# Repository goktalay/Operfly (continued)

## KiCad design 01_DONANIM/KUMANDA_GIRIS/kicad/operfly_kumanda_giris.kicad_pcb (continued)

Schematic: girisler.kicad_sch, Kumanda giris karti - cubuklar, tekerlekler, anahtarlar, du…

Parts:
C13, C14, C15, C16, C17, C18, C19, C20, C21, C22, C23, C24, C25, C26, C27, C28: 100n; C_0402_1005Metric
J3: Cubuk sol; JST_GH_SM04B-GHS-TB_1x04-1MP_P1.25mm_Horizontal
J4: Cubuk sag; JST_GH_SM04B-GHS-TB_1x04-1MP_P1.25mm_Horizontal
J5: Tekerlek sol; JST_GH_SM03B-GHS-TB_1x03-1MP_P1.25mm_Horizontal
J6: Tekerlek sag; JST_GH_SM03B-GHS-TB_1x03-1MP_P1.25mm_Horizontal
J7: Anahtar A; JST_GH_SM03B-GHS-TB_1x03-1MP_P1.25mm_Horizontal
J8: Anahtar B; JST_GH_SM03B-GHS-TB_1x03-1MP_P1.25mm_Horizontal
J9: Anahtar C; JST_GH_SM03B-GHS-TB_1x03-1MP_P1.25mm_Horizontal
J10: Anahtar D; JST_GH_SM03B-GHS-TB_1x03-1MP_P1.25mm_Horizontal
J11: Anahtar E; JST_GH_SM03B-GHS-TB_1x03-1MP_P1.25mm_Horizontal
J12: Anahtar F; JST_GH_SM03B-GHS-TB_1x03-1MP_P1.25mm_Horizontal
J13: Yon tusu; JST_GH_SM06B-GHS-TB_1x06-1MP_P1.25mm_Horizontal
J14: Dugme 1; JST_GH_SM02B-GHS-TB_1x02-1MP_P1.25mm_Horizontal
J15: Dugme 2; JST_GH_SM02B-GHS-TB_1x02-1MP_P1.25mm_Horizontal
R15, R16, R17, R18, R19, R21, R25, R28, R31, R34, R37, R40, R48, R50: 1k; R_0402_1005Metric
R20, R22: 1M; R_0402_1005Metric
R23, R24, R26, R27, R29, R30, R32, R33, R35, R36, R38, R39: 47k; R_0402_1005Metric
R41, R45, R47, R49: 10k; R_0402_1005Metric
R42: 0R; R_0402_1005Metric
R43: 2k2; R_0402_1005Metric
R44: 4k7; R_0402_1005Metric
R46: 22k; R_0402_1005Metric

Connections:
+3V3: R47.1, R49.1; also elsewhere on the board
+3V3A: C17.1, J3.1, J4.1, J5.1, J6.1, J7.1, J8.1, J9.1, J10.1, J11.1, J12.1, R23.1, R26.1, R29.1, R32.1, R35.1, R38.1, R41.1; also elsewhere on the board
BTN_1: C27.1, R47.2, R48.2; also elsewhere on the board
BTN_1_J: J14.1, R48.1
BTN_2: C28.1, R49.2, R50.2; also elsewhere on the board
BTN_2_J: J15.1, R50.1
GIM_L_X: C13.1, R15.2; also elsewhere on the board
GIM_L_X_J: J3.2, R15.1
GIM_L_Y: C14.1, R16.2; also elsewhere on the board
GIM_L_Y_J: J3.3, R16.1
GIM_R_X: C15.1, R17.2; also elsewhere on the board
GIM_R_X_J: J4.2, R17.1
GIM_R_Y: C16.1, R18.2; also elsewhere on the board
GIM_R_Y_J: J4.3, R18.1
GND: C13.2, C14.2, C15.2, C16.2, C17.2, C18.2, C19.2, C20.2, C21.2, C22.2, C23.2, C24.2, C25.2, C26.2, C27.2, C28.2, J3.4, J3.MP (MountPin), J4.4, J4.MP (MountPin), J5.3, J5.MP (MountPin), J6.3, J6.MP (MountPin), J7.3, J7.MP (MountPin), J8.3, J8.MP (MountPin), J9.3, J9.MP (MountPin), J10.3, J10.MP (MountPin), J11.3, J11.MP (MountPin), J12.3, J12.MP (MountPin), J13.1, J13.MP (MountPin), J14.2, J14.MP (MountPin), J15.2, J15.MP (MountPin), R20.2, R22.2, R24.2, R27.2, R30.2, R33.2, R36.2, R39.2; also elsewhere on the board
NAV_ADC: C26.1, R41.2, R42.2, R43.2, R44.2, R45.2, R46.2; also elsewhere on the board
NAV_C: J13.2, R42.1
NAV_D: J13.4, R44.1
NAV_L: J13.5, R45.1
NAV_R: J13.6, R46.1
NAV_U: J13.3, R43.1
SW_A: C20.1, R25.2; also elsewhere on the board
SW_A_J: J7.2, R23.2, R24.1, R25.1
SW_B: C21.1, R28.2; also elsewhere on the board
SW_B_J: J8.2, R26.2, R27.1, R28.1
SW_C: C22.1, R31.2; also elsewhere on the board
SW_C_J: J9.2, R29.2, R30.1, R31.1
SW_D: C23.1, R34.2; also elsewhere on the board
SW_D_J: J10.2, R32.2, R33.1, R34.1
SW_E: C24.1, R37.2; also elsewhere on the board
SW_E_J: J11.2, R35.2, R36.1, R37.1
SW_F: C25.1, R40.2; also elsewhere on the board
SW_F_J: J12.2, R38.2, R39.1, R40.1
WHEEL_L: C18.1, R19.2, R20.1; also elsewhere on the board
WHEEL_L_J: J5.2, R19.1
WHEEL_R: C19.1, R21.2, R22.1; also elsewhere on the board
WHEEL_R_J: J6.2, R21.1

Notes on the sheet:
DUGMELER (anlik basmali, 2 adet): 2 kontak = sinyal, GND. 10 k yukari cekme, 100 nF.
Secilen gimbalin kendi kablosu bu siraya gore uyarlanir. Her giriste 1 k + 100 nF: suzme ve asiri gerilimde akim sinirlama.
TEKERLEKLER (potansiyometre ya da Hall, analog): 3 kontak = +3V3A, sinyal, GND.
bos 3,3 V; orta 0 V; yukari 0,60 V; asagi 1,06 V; sol 1,65 V; sag 2,27 V (10 k yukari cekme ile).
YON TUSU (5 yonlu, menu icin): 6 kontak = GND, orta, yukari, asagi, sol, sag. Her yon farkli direncle tek analog girise baglanir:
CUBUKLAR (Hall etkili gimbal, 3,3 V, eksen basina analog cikis): 4 kontak = +3V3A, X, Y, GND (bizim tanimimiz).
orta konumda iki 47 k giris gerilimini yariya ceker. Tek analog giris uc konumu okur; kopuk kablo da 'orta' gorunur (ariza anlasilir).
ANAHTARLAR A-F (2 ya da 3 konumlu): 3 kontak = +3V3A, ortak uc, GND. Anahtar ortak ucu +3V3A'ya ya da GND'ye baglar;

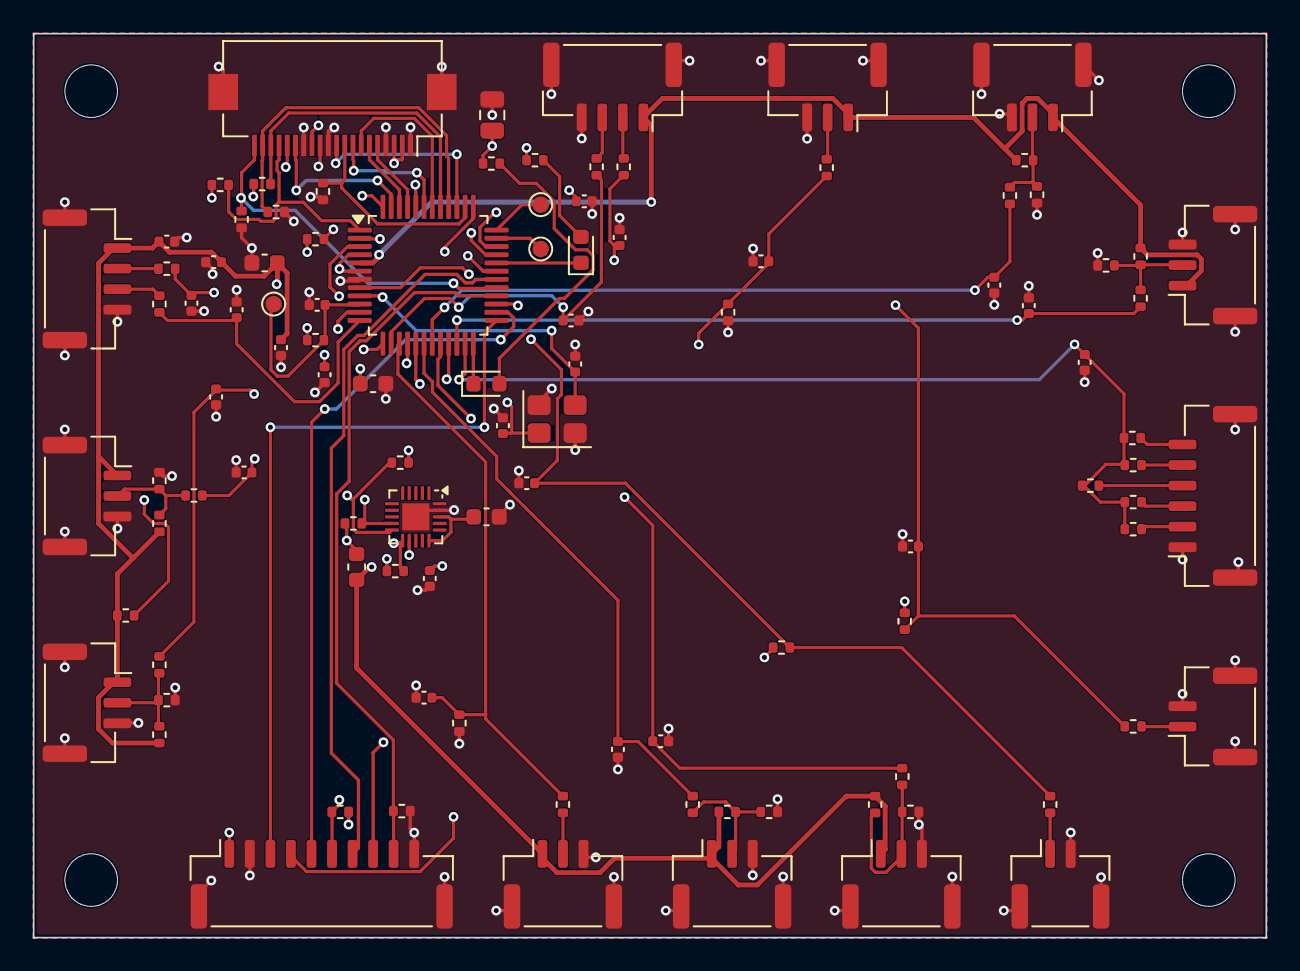
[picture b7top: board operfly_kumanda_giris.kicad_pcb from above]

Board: 4 copper layers, 75.0 x 55.0 mm, 106 parts (0 on the bottom side), 69 nets.

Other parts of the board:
H1, H2, H3, H4: M3; MountingHole_3.2mm_M3

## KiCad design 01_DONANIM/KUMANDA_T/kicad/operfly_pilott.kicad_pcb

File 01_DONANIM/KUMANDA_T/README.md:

# Operfly Pilot T ana kartı (OPFKTL)

12 kanal kumanda eden ve telemetriyi küçük ekranda gösteren model. Bu kart Pilot 12 ana kartının devresini
(batarya, şarj, beslemeler, kumanda radyosu) ve telemetri ekranını taşır; işlemci ve güvenli eleman ortak giriş
kartındadır (`01_DONANIM/KUMANDA_GIRIS`). İki kart arasındaki bağlantı: `13_DOKUMANTASYON/KUMANDA_ARAYUZU.md`.

## Durum (15 Kasım 2026)

- KiCad projesi: `kicad/operfly_pilott.kicad_pro`.
  Üretim ve denetim: `python 10_ORTAK_ARACLAR/kicad/denetle.py KUMANDA_T operfly_pilott`.
- Şematik tamam, 4 sayfa: kök, batarya/şarj/USB/güç/3,3 V (`guc`), radyo ve giriş kartı bağlantısı (`radyo`),
  ekran (`ekran`). ERC 0 hata, 0 uyarı. Kart çizimi başlamadı.
- `guc` ve `radyo` sayfaları Pilot 12 ile ortak kaynaktan üretilir (`10_ORTAK_ARACLAR/kicad/kumanda_ana.py`);
  o sayfaların kararları ve doğrulama listesi `01_DONANIM/KUMANDA_12/README.md` dosyasındadır ve burada da geçerlidir.

## Kararlar (sahibi kararı tasarımcıya bıraktı)

1. **Pilot T = Pilot 12 + ekran.** Güç ve radyo bölümü birebir aynıdır; tek kaynak dosyadan üretilir, bir karttaki
   düzeltme diğerine kendiliğinden geçer. Telemetri kumanda radyosunun aynı bağlantısından gelir; ek radyo yoktur.
2. **Ekran: EA DOGM128W-6** (128 × 64 nokta, görünen alan 51 × 31 mm, siyah-beyaz, yarı geçirgen LCD). Gerekçe:
   güneş altında arka ışıksız okunur (renkli küçük ekranlar güneşte okunmaz), 0,3 mA çeker (batarya süresini
   etkilemez), tek 3,3 V besleme ve SPI ile çalışır, karta doğrudan lehimlenir, tek adet satın alınabilir.
   Telemetri için yeterlidir: 8 satır × 21 karakter ya da büyük rakamlarla 4 satır.
3. **Arka ışık: kehribar (EA LED55X46-A).** 3,3 V'tan yalnızca dirençle çalışır (beyaz arka ışık yükselten sürücü
   isterdi), ömrü 100.000 saattir ve gece gözü kamaştırmaz. İşlemci PWM ile kısar; gündüz kapalı kalabilir.
   Toplam yaklaşık 45 mA.
4. **Ekranı giriş kartındaki işlemci sürer.** Giriş kartının "ekran / genişleme" konnektöründen bu karta 10 telli
   düz kablo gelir (JST-GH 10, iki uçta aynı sıra). Böylece giriş kartı üç kumandada da değişmeden kalır.
5. **Ekran bu kartın 3,3 V'undan beslenir;** kablodaki 3,3 V ucu kullanılmaz (iki besleme yolu birleştirilmez).
6. **Güvenli durum:** kablo takılı değilken ya da işlemci sıfırlanırken ekran sıfırlamada tutulur, arka ışık kapalıdır.
7. **Ekranın iç gerilim yükselticisi kullanılır** (üreticinin tek beslemeli devresi, 9 adet 1 µF kondansatör);
   ayrı bir 12 V kaynağı gerekmez.

## Sahibinin bilmesi gerekenler

- **Ekran küçük ve tek renklidir;** harita ya da video göstermez. Harita ve video Pilot Pro'nun işidir.
- **Ekran ana kartın üstündedir;** kasada ekran penceresi ana kartın yerini belirler. Kasa tasarımında ekranın
  ayrı küçük bir karta alınması gerekirse devre aynen taşınır.
- **Ekran karta elle lehimlenir** (LCD fırın lehimine dayanmaz; üretici 80 °C üstünü yasaklar). Dizgi sonrasında
  ayrı bir işçilik adımıdır.
- **Soğukta ekran yavaşlar:** çalışma aralığı −20…+70 °C. Daha soğukta görüntü geç değişir; kumanda çalışmaya
  devam eder (ekran kumanda yolunun parçası değildir).
- **Çalışma süresi Pilot 12 ile hemen hemen aynıdır;** arka ışık sürekli açıkken yaklaşık 45 mA ek tüketim olur.

## Doğrulanacaklar

- **Ayak izi** (KiCad kütüphanesindeki `Display:EA_DOGM128-6`) üreticinin ölçü çizimiyle ve arka ışıklı yükseklikle
  (5,8 mm) karşılaştırılacak; ekranın bakış yönü (alttan / üstten) kasaya göre seçilecek (yazılım ayarı).
- **Arka ışık akımı ve parlaklığı** numunede ölçülecek; 82 Ω dirençler ve anahtarlama transistörü buna göre
  kesinleşecek. Gece görüş gözlüğüyle kullanım istenirse arka ışık rengi ve en düşük parlaklık ayrıca denenecek.
- **Kontrast ayarı** sıcaklık aralığında numunede denenecek.
- **Askeri sıcaklık aralığı hedefi** (−40 °C) bu ekranla karşılanmaz; gerekirse ısıtıcılı ya da geniş aralıklı
  ekran ayrıca değerlendirilecek.
- **Kablo boyu ve SPI hızı:** 10 telli kablo kısa tutulacak (öneri 10 cm altı); 33 Ω seri dirençlerle denenecek.
- Güç ve radyo bölümünün doğrulama listesi: `01_DONANIM/KUMANDA_12/README.md`.

## Kart çizimi (otomatik)

Sahibinin kararıyla kart **otomatik** çizildi: yerleşim `pcb_yerlesim.py`, yollar dış bir otomatik yol çiziciyle
(`pcb_ciz.py`). Dosya: `kicad/operfly_pilott.kicad_pcb`; ayarlar `kicad/pcb_ayar.py`.
Yeniden üretmek için: `python 10_ORTAK_ARACLAR/kicad/pcb_ciz.py KUMANDA_T operfly_pilott`.

- **Kart:** 135 x 95 mm, 4 katman (üst: elemanlar + sinyal, iç 1: toprak, iç 2: +3V3, alt: sinyal), 100 eleman, tamamı üst yüzde; köşelerde M3 montaj deliği.
- **Kurallar:** yol 0,20 mm, açıklık 0,125 mm, geçiş 0,6/0,3 mm; besleme ağları, ağın en dar ucunu aşmayacak biçimde 0,2-1,0 mm (0,4 mm ve üstünde geçiş 0,8/0,4 mm); bakır-kenar 0,25 mm.
- **Denetim:** DRC 0 ihlal, 0 bağlanmamış uç; şematik-kart uyumu temiz. 857 yol parçası, 151 geçiş.

**Bu bir mühendis çizimi değildir.** Üretimden önce bir kart tasarımcısının bakması gereken noktalar:

- Anten hatları 0,35 mm genişlikte çizildi; 50 ohm empedans üreticinin katman dizilimiyle hesaplanıp doğrulanmadı, hat uzunluğu, kıvrımlar ve geçiş sayısı gözetilmedi. Menzil doğrudan bu hatlara bağlıdır.
- Kenar montajlı SMA konnektörlerinin uçları kart kenarından 0,35 mm içeride başlar; anten hatlarının çevresinde toprak dikiş geçişleri yok.
- Ekranın (EA DOGM128) kart üzerindeki yeri kasadaki ekran penceresine göre seçilmedi; ekranın altında kalan elemanların yüksekliği denetlenmedi.
- Şarj devresi ve regülatörlerin ısıl bakırı ve akım yolları ayrıca hesaplanmadı.
- Kart ölçüsü ve konnektör yerleri kumanda kasasına göre seçilmedi (kasa henüz tasarlanmadı).
- Anahtarlamalı regülatörlerin (bobin, diyot, giriş/çıkış kondansatörleri) akım döngüleri küçük tutulmadı; gürültü ve verim ölçülmeli.
- Kristal ve osilatör hatları en kısa yoldan çizilmedi; altlarından başka sinyal geçip geçmediğine bakılmalı.
- Fark çiftleri (CAN, USB, Ethernet) çift olarak, eşit uzunlukta ve empedans denetimli çizilmedi.
- Güç elemanlarının soğutma bakırı ve ısıl geçişleri ayrıca hesaplanmadı.
- Eleman adları üretim katmanında bırakıldı; kart üstünde yazı (serigrafi) yok.
- Kasa, konnektör yerleri ve montaj delikleri mekanik tasarımla eşleştirilmedi.
- Üretim dosyaları (Gerber, delik, dizgi) henüz çıkarılmadı.

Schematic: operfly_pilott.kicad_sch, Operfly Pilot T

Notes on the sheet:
Sematik betikle uretilir: 01_DONANIM/KUMANDA_T/kicad/uret.py. Islemci giris kartindadir.
Operfly Pilot T - kumanda ana karti (OPFKTL)

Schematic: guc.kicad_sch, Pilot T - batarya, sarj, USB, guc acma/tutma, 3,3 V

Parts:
BZ1: PKLCS1212E4001; Buzzer_Murata_PKLCS1212E
C1: 4u7 25V; C_0805_2012Metric
C2, C3, C7, C10, C12: 100n; C_0402_1005Metric
C4, C5, C11, C13, C14: 10u 10V; C_0805_2012Metric
C6: 22u 10V; C_1206_3216Metric
C8: 1u; C_0402_1005Metric
C9: 470n; C_0402_1005Metric
D1: USBLC6-2P6; SOT-666
D2: LED turuncu (sarj); LED_0603_1608Metric
D3: BAT54C; SOT-23
J1: USB Type-C; USB_C_Receptacle_GCT_USB4105-xx-A_16P_TopMnt_Horizontal
J2: Batarya (JST-XH); JST_XH_B3B-XH-A_1x03_P2.50mm_Vertical
J3: Guc dugmesi; JST_GH_SM02B-GHS-TB_1x02-1MP_P1.25mm_Horizontal
L1: 2u2 XAL4020-222; L_Coilcraft_XAL4020-XXX
Q1, Q2, Q3, Q4: 2N7002; SOT-23
R1, R2: 5k1 1%; R_0402_1005Metric
R3, R4, R16: 10k; R_0402_1005Metric
R5: 40k2 1%; R_0402_1005Metric
R6: 10k 1%; R_0402_1005Metric
R7, R8, R17, R18, R22: 100k; R_0402_1005Metric
R9: 10m 1% 1W; R_1206_3216Metric
R10: 0R; R_0402_1005Metric
R11: 10k DNP; R_0402_1005Metric; not fitted
R12: 887R 1%; R_0402_1005Metric
R13: 1k18 1%; R_0402_1005Metric
R14: 68k 1%; R_0402_1005Metric
R15: 1k5; R_0402_1005Metric
R19: 220k; R_0402_1005Metric
R20: 100R; R_0402_1005Metric
R21: 1k; R_0402_1005Metric
TP1: SYSOFF; TestPoint_Pad_D1.0mm
U1: LMV393; TSSOP-8_4.4x3mm_P0.65mm
U2: BQ24075RGT; VQFN-16-1EP_3x3mm_P0.5mm_EP1.6x1.6mm
U3: BQ27441DRZR-G1A; Texas_S-PDSO-N12
U4: TPS63001DRC; Texas_DRC0010J_ThermalVias

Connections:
+3V3: C3.1, C13.1, C14.1, R5.1, R7.1, R8.1, U1.8 (V+), U4.1 (VOUT), U4.10 (FB); also elsewhere on the board
+BATT: C4.1, C8.1, J2.1, R9.1, U3.6 (BAT), U3.8 (SRP)
+BAT_CHG: C5.1, R9.2, U2.2 (BAT), U2.3 (BAT), U3.7 (SRN)
+SYS: BZ1.1 (+), C6.1, C7.1, C11.1, R15.1, R20.1, R21.1, U2.10 (OUT), U2.11 (OUT), U4.5 (VIN), U4.6 (EN), U4.7 (PS/SYNC); also elsewhere on the board
ALERT_N: U3.12 (GPOUT); also elsewhere on the board
BAT_NTC: J2.2, R10.1
BUZZER: Q4.1 (G), R22.1; also elsewhere on the board
BUZZER_K: BZ1.2 (-), Q4.3 (D), R21.2
CC1_F: R3.2, U1.2 (-)
CC2_F: R4.2, U1.6 (-)
CC_REF: C2.1, R5.2, R6.1, U1.3 (+), U1.5 (+)
CHG_EN2: Q1.3 (D), R8.2, U2.5 (EN2)
CHG_ILIM: R13.1, U2.12 (ILIM)
CHG_ISET: R12.1, U2.16 (ISET)
CHG_LED_A: D2.2 (A), R15.2
CHG_LED_K: D2.1 (K), U2.9 (~CHG)
CHG_TMR: R14.1, U2.14 (TMR)
CHG_TS: R10.2, R11.1, U2.1 (TS)
GAUGE_BIN: R16.1, U3.10 (BIN)
GAUGE_VDD: C9.1, U3.5 (V_{DD})
GND: C1.2, C2.2, C3.2, C4.2, C5.2, C6.2, C7.2, C8.2, C9.2, C10.2, C11.2, C12.2, C13.2, C14.2, D1.2 (GND), J1.A1 (GND), J1.A12 (GND), J1.B1 (GND), J1.B12 (GND), J1.SH (SHIELD), J2.3, J3.2, J3.MP (MountPin), Q1.2 (S), Q2.2 (S), Q3.2 (S), Q4.2 (S), R1.2, R2.2, R6.2, R11.2, R12.2, R13.2, R14.2, R16.2, R17.2, R19.2, R22.2, U1.4 (V-), U2.4 (~CE), U2.8 (VSS), U2.17 (VSS), U3.3 (V_{SS}), U3.13 (PAD), U4.3 (PGND), U4.9 (GND), U4.11 (PGND); also elsewhere on the board
HICUR_N: Q1.1 (G), R7.2, U1.1, U1.7, U2.6 (EN1)
I2C_SCL: U3.2 (SCL); also elsewhere on the board
I2C_SDA: U3.1 (SDA); also elsewhere on the board
L1_3V3: L1.1, U4.4 (L1)
L2_3V3: L1.2, U4.2 (L2)
PWR_BTN: C10.1, D3.3, J3.1
PWR_BTN_N: D3.2; also elsewhere on the board
PWR_HOLD: Q2.1 (G), R17.1; also elsewhere on the board
SYSOFF: D3.1, Q2.3 (D), Q3.3 (D), TP1.1, U2.15 (SYSOFF)
USB_CC1: J1.A5 (CC1), R1.1, R3.1
USB_CC2: J1.B5 (CC2), R2.1, R4.1
USB_DM: D1.3 (I/O2), D1.4 (I/O2), J1.A7 (D-), J1.B7 (D-); also elsewhere on the board
USB_DP: D1.1 (I/O1), D1.6 (I/O1), J1.A6 (D+), J1.B6 (D+); also elsewhere on the board
VBUS_SENS: Q3.1 (G), R18.2, R19.1
VBUS_USB: C1.1, D1.5 (VBUS), J1.A4 (VBUS), J1.A9 (VBUS), J1.B4 (VBUS), J1.B9 (VBUS), R18.1, U2.13 (IN)
VINA_3V3: C12.1, R20.2, U4.8 (VINA)

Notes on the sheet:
Sarj akimi 890 / 887R = 1,0 A; giris siniri 1610 / 1k18 = 1,36 A; guvenlik zamanlayicisi 10 x 48 s x 68 = 9 saat.
SESLI UYARICI (piezo): islemcinin BUZZER cikisi transistorle surer; 1 k paralel direnc piezoyu bosaltir.
USB TYPE-C: sarj girisi + islemcinin USB'si (yassi kablodan giris kartina). CC uclarinda 5,1 k: kart tuketicidir.
3,3 V (TPS63001, alcaltan-yukselten, sabit 3,3 V): giris 3,0-5,5 V araliginin tamaminda calisir. Sabit frekans (PS = 1).
direncle ayarli 1,36 A sinirinda (EN2=1, EN1=0) calisir. HICUR_N: 0 = kaynak en az 1,5 A verebiliyor.
SYSOFF = 1 bataryayi sistemden ayirir (kapali durum). CHG isigi sarj surerken yanar.
BATARYA OLCER (bq27441-G1A): kalan kapasiteyi ve gerilimi I2C'den verir; GPOUT -> ALERT_N. Yukari cekmeler giris kartinda.
GUC ACMA / TUTMA: kapaliyken SYSOFF ic direncle yuksektir. Dugme SYSOFF'u diyot uzerinden sifira ceker -> sistem acilir;
SARJ ve GUC YOLU (BQ24075): USB varken sistemi USB'den besler ve bataryayi sarj eder; USB yokken bataryadan besler.
Esik 0,66 V. Standart kaynakta sarj entegresi 0,5 A giris sinirinda (EN2=0, EN1=1), 1,5 A / 3 A bildiren kaynakta
KAYNAK AKIMI ALGILAMA (LMV393): Type-C kaynagi verebildigi akimi CC gerilimiyle bildirir (standart < 0,61 V; 1,5 A > 0,70 V).
BATARYA (tek hucreli Li-ion paket, koruma devreli, 10 k NTC'li): 3 kontak = +, NTC, -. Olcer icin 10 mOhm seri direnc.
islemci PWR_HOLD = 1 ile tutar, 0 yapinca kapanir. USB takiliyken SYSOFF kendiliginden sifirdadir (sarj islemciye bagli degil).
Cift diyot dugmeyi iki hatta ayri ayri baglar: kapaliyken giris kartindaki yukari cekme SYSOFF'u etkilemez.

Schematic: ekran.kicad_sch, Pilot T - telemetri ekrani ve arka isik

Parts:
C23: 100n; C_0402_1005Metric
C24: 1u; C_0603_1608Metric
C25, C26, C27, C28, C29, C30, C31, C32, C33: 1u 25V; C_0603_1608Metric
DS1: EA DOGM128W-6 + EA LED55X46-A; EA_DOGM128-6
J7: Ekran kablosu (giris karti); JST_GH_SM10B-GHS-TB_1x10-1MP_P1.25mm_Horizontal
Q6: 2N7002; SOT-23
R30, R31: 33R; R_0402_1005Metric
R32, R37: 100k; R_0402_1005Metric
R33: 10k; R_0402_1005Metric
R34, R35, R36: 82R; R_0402_1005Metric

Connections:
+3V3: C23.1, C24.1, DS1.34 (VDD2), DS1.35 (VDD), R32.1, R34.1, R35.1, R36.1; also elsewhere on the board
BL_A1: DS1.1 (A1+), R34.2
BL_A2: DS1.2 (A2+), R35.2
BL_A3: DS1.3 (A3+), R36.2
BL_K: DS1.18 (C1-), DS1.19 (C2-), DS1.20 (C3-), Q6.3 (D)
DISP_BL: J7.9, Q6.1 (G), R37.1
DISP_CS: DS1.40 (~CS1B), J7.6, R32.2
DISP_DC: DS1.38 (A0), J7.7
DISP_MOSI: J7.4, R31.1
DISP_RST: DS1.39 (~RST), J7.8, R33.1
DISP_SCK: J7.3, R30.1
GND: C23.2, C24.2, C28.2, C29.2, C30.2, C31.2, C32.2, C33.2, DS1.26 (VSS), DS1.33 (VSS), J7.2, J7.10, J7.MP (MountPin), Q6.2 (S), R33.2, R37.2; also elsewhere on the board
LCD_C1N: C25.2, C26.2, DS1.30 (CAP1N)
LCD_C1P: C26.1, DS1.29 (CAP1P)
LCD_C2N: C27.2, DS1.27 (CAP2N)
LCD_C2P: C27.1, DS1.28 (CAP2P)
LCD_C3P: C25.1, DS1.31 (CAP3P)
LCD_SCL: DS1.37 (SCL), R30.2
LCD_SI: DS1.36 (SI), R31.2
LCD_V0: C29.1, DS1.21 (V0)
LCD_V1: C30.1, DS1.22 (V1)
LCD_V2: C31.1, DS1.23 (V2)
LCD_V3: C32.1, DS1.24 (V3)
LCD_V4: C33.1, DS1.25 (V4)
LCD_VOUT: C28.1, DS1.32 (VOUT)

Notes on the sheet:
GIRIS KARTINDAN GELEN EKRAN KABLOSU (JST-GH 10, duz kablo): uc sirasi giris kartindaki 'ekran / genisleme' konnektoruyle ayni.
6 CS, 7 DC -> A0, 8 RST, 9 BL (arka isik, PWM), 10 GND.
ARKA ISIK (kehribar, uc LED yolu, yol basina 82R ile yaklasik 15 mA): 3,3 V'tan dogrudan calisir. DISP_BL = 1 yakar;
EKRAN (EA DOGM128W-6, tek besleme 3,3 V): ic gerilim yukseltici 9 adet 1 uF kondansator ister (uretici devresi).
1 +3V3 (kullanilmaz: ekran bu kartin 3,3 V'undan beslenir), 2 GND, 3 SCK, 4 MOSI, 5 MISO (kullanilmaz: ekran yalniz yazilir),
islemci PWM ile kisar. Gunduz kapali kalabilir (ekran arka isiksiz okunur).
RST dusukken ekran sifirlamadadir (kablo takili degilken ya da islemci sifirlanirken 10k tutar). Kontrast yazilimla ayarlanir.

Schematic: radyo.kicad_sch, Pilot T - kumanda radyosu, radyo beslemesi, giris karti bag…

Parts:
C15, C18, C20, C21, C22: 22u 10V; C_1206_3216Metric
C16: 100n; C_0402_1005Metric
C17: 100p; C_0402_1005Metric
C19: 10n; C_0402_1005Metric
J4: ANT 1 (SMA); SMA_Amphenol_132289_EdgeMount
J5: ANT 2 (SMA); SMA_Amphenol_132289_EdgeMount
J6: Giris karti (FFC 20); Hirose_FH12-20S-0.5SH_1x20-1MP_P0.50mm_Horizontal
L2: 1u0 XAL4020-102; L_Coilcraft_XAL4020-XXX
Q5: 2N7002; SOT-23
R23, R24, R25: 470R; R_0402_1005Metric
R26: 422k 1%; R_0402_1005Metric
R27: 100k 1%; R_0402_1005Metric
R28, R29: 100k; R_0402_1005Metric
TP2: RADIO_SWO; TestPoint_Pad_D1.0mm
TP3: RADIO_3V3; TestPoint_Pad_D1.0mm
TP4: RADIO_TXD; TestPoint_Pad_D1.0mm
U5: RFD900ux-SMT (secenek: RFD868ux-SMT); RFDesign_RFD900ux-SMT
U6: TPS61230DRC; Texas_S-PVSON-N10_ThermalVias

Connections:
+3V3: J6.2, J6.3; also elsewhere on the board
+5V_RADIO: C15.1, C16.1, C17.1, C20.1, C21.1, C22.1, R26.1, U5.19 (+5V), U6.3 (VOUT), U6.4 (VOUT)
+SYS: C18.1, L2.1, R28.1, U6.10 (VIN); also elsewhere on the board
ALERT_N: J6.17; also elsewhere on the board
BUZZER: J6.20; also elsewhere on the board
EN_RADIO: Q5.3 (D), R28.2, U6.9 (EN)
FB_RADIO: R26.2, R27.1, U6.7 (FB)
GND: C15.2, C16.2, C17.2, C18.2, C19.2, C20.2, C21.2, C22.2, J4.2 (Ext), J5.2 (Ext), J6.1, J6.4, J6.11, J6.14, J6.MP (MountPin), Q5.2 (S), R27.2, R29.2, U5.8 (GND), U5.9 (GND), U5.11 (GND), U5.12 (GND), U5.14 (GND), U5.15 (GND), U5.17 (GND), U5.18 (GND), U5.20 (GND), U5.29 (GND), U5.30 (GND), U6.11 (GND); also elsewhere on the board
I2C_SCL: J6.15; also elsewhere on the board
I2C_SDA: J6.16; also elsewhere on the board
PWR_BTN_N: J6.18; also elsewhere on the board
PWR_HOLD: J6.19; also elsewhere on the board
RADIO_3V3: TP3.1, U5.10 (+3V3_OUT)
RADIO_ANT1: J4.1 (In), U5.13 (ANT1)
RADIO_ANT2: J5.1 (In), U5.16 (ANT2)
RADIO_BOOT_N: J6.10, R25.1
RADIO_CTS: J6.7, R24.1
RADIO_CTS_M: R24.2, U5.28 (CTS)
RADIO_OFF: J6.9, Q5.1 (G), R29.1
RADIO_RTS: J6.8, U5.27 (RTS)
RADIO_RXD: J6.5, R23.1
RADIO_RX_M: R23.2, U5.25 (RX)
RADIO_SWO: R25.2, TP2.1, U5.4 (SWO)
RADIO_TXD: J6.6, TP4.1, U5.26 (TX)
SS_RADIO: C19.1, U6.6 (SS)
SW_RADIO: L2.2, U6.1 (SW), U6.2 (SW)
USB_DM: J6.12; also elsewhere on the board
USB_DP: J6.13; also elsewhere on the board

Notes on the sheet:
RADYO BESLEMESI (TPS61230, yukselten): +SYS (3,0-5,5 V) -> 5,2 V. Modul verirken 1 A tepe ceker; entegre 3,3 V giristen 2,1 A verebilir.
Besleme sifirlamada ACIKTIR; islemci RADIO_OFF = 1 ile keser. Devre ureticinin 5 V ornek devresidir.
KUMANDA RADYO MODULU (RFD900ux-SMT; 868 MHz icin RFD868ux-SMT). Baglanti RX kartindakinin aynisi:
islemciden gelen hatlarda 470R, SWO ucu yazilim yukleme kipi icin islemcide (RADIO_BOOT_N).
Cikis = 1,0 V x (1 + 422k / 100k) = 5,22 V. Giris cikistan yuksekse (USB'de) entegre girisi dogrudan cikisa aktarir (en cok 5,5 V).
GIRIS KARTI BAGLANTISI (20 kontakli yassi kablo): uc sirasi 13_DOKUMANTASYON/KUMANDA_ARAYUZU.md ile birebir.

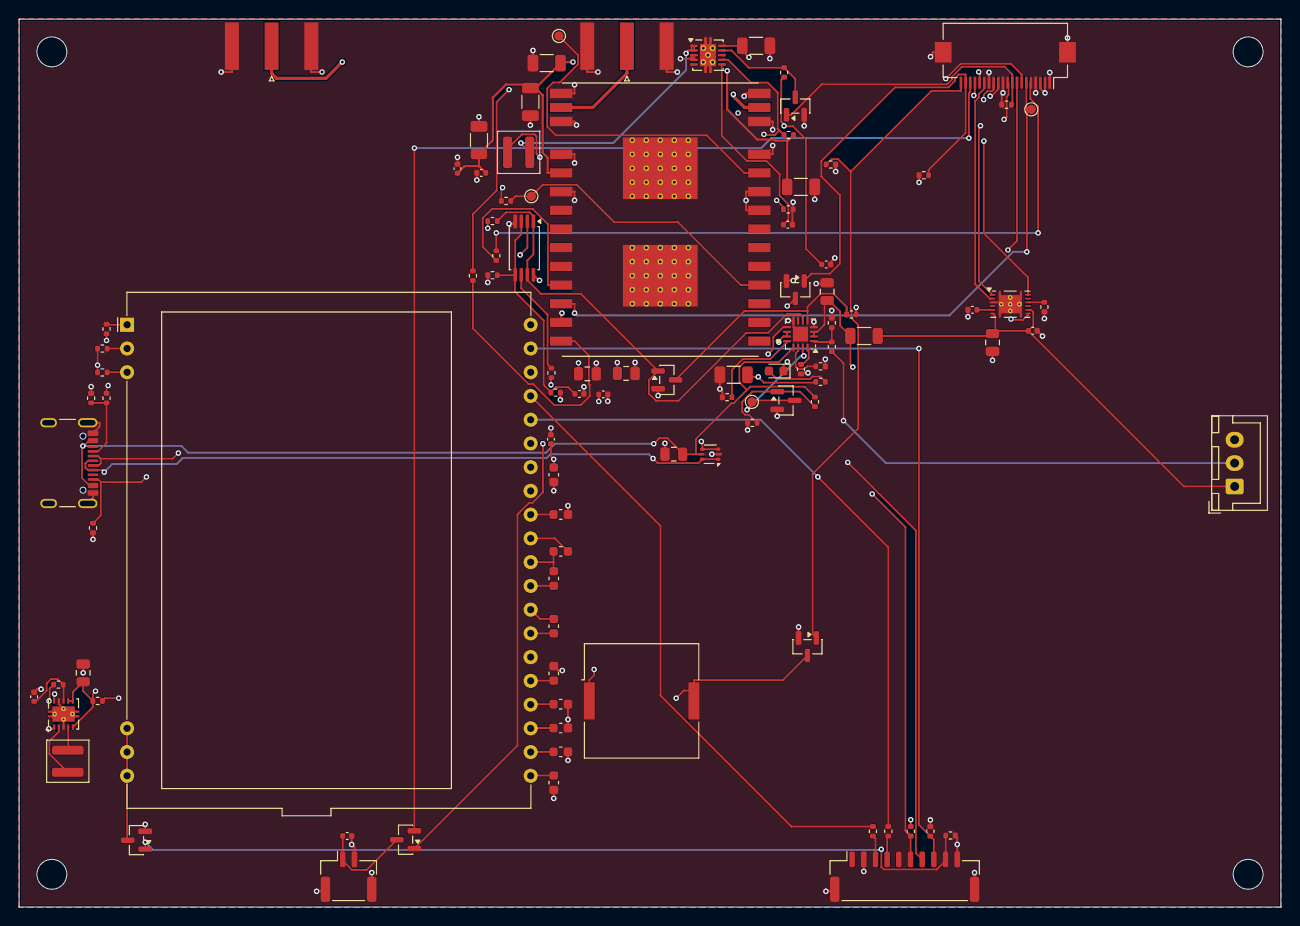
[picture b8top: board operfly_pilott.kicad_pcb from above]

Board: 4 copper layers, 135.0 x 95.0 mm, 104 parts (0 on the bottom side), 77 nets.

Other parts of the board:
H1, H2, H3, H4: M3; MountingHole_3.2mm_M3

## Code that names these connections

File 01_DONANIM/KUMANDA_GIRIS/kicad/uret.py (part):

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
# İşlemci pinleri (KiCad pin verisindeki alternatif işlevlerle denetlendi).
PINLER = {
    "PA0": "GIM_L_X", "PA1": "GIM_L_Y", "PA2": "GIM_R_X", "PA3": "GIM_R_Y",        # ADC1_IN0..3
    "PA4": "WHEEL_L", "PA5": "WHEEL_R",                                            # ADC1_IN4, IN5
    "PA6": "SW_A", "PA7": "SW_B", "PB0": "SW_C", "PB1": "SW_D", "PB2": "SW_E", "PB10": "SW_F",   # ADC1_IN6..11
    "PB11": "NAV_ADC",                                                             # ADC1_IN15
    "PB6": "RADIO_RXD", "PB7": "RADIO_TXD",                                        # USART1_TX -> radyo RX, USART1_RX <- radyo TX
    "PB3": "RADIO_CTS", "PB4": "RADIO_RTS",                                        # USART1_RTS -> radyo CTS, USART1_CTS <- radyo RTS
    "PA9/PA11": "USB_DM", "PA10/PA12": "USB_DP",                                   # USB (PA11 = D-, PA12 = D+)
    "PB8": "I2C_SCL", "PB9": "I2C_SDA", "PB5": "SE_ENA",                           # I2C1: guvenli eleman + ana kart
    "PB13": "DISP_SCK", "PB14": "DISP_MISO", "PB15": "DISP_MOSI",                  # SPI2
    "PA15": "DISP_CS", "PC6": "DISP_DC", "PC7": "DISP_RST", "PA8": "DISP_BL",      # PA8 = TIM1_CH1
    "PD0": "RADIO_OFF", "PD1": "RADIO_BOOT_N", "PD2": "PWR_HOLD", "PD3": "PWR_BTN_N", "PC13": "ALERT_N",
    "PC14": "BTN_1", "PC15": "BTN_2",
    "PA9/UCPD1_DBCC1": "BUZZER",                                                   # TIM1_CH2
    "PA10/UCPD1_DBCC2": "LED_DURUM", "PB12": "LED_UYARI",
    "PA13": "SWDIO", "PA14": "SWCLK", "PF0": "HSE_IN", "PF1": "HSE_OUT", "PF2": "NRST",
    "VDD": "+3V3", "VBAT": "+3V3", "VREF+": "+3V3A", "VSS": "GND",
}

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g = Izgara(200, 80, sutun=10)
for deger in ("4u7", "100n", "100n"):
    k.C(ic, g, deger, "+3V3", fp=C0603 if deger == "4u7" else "Capacitor_SMD:C_0402_1005Metric")
k.koy(ic, "Device:Crystal_GND24", "Y", "16 MHz", *g.yer(), {"1": "HSE_IN", "3": "HSE_OUT", "2": "GND", "4": "GND"}, "Crystal:Crystal_SMD_3225-4Pin_3.2x2.5mm")
k.C(ic, g, "10p", "HSE_IN"); k.C(ic, g, "10p", "HSE_OUT")
k.R(ic, g, "10k", "+3V3", "NRST"); k.C(ic, g, "100n", "NRST")
g.satir()
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
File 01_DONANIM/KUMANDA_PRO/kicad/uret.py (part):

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kok.metin("Operfly Pilot Pro - kumanda ana karti (OPFKPR)", 25.4, 25.4, 3.0)
kok.metin("Sematik betikle uretilir: 01_DONANIM/KUMANDA_PRO/kicad/uret.py. Ekran arayuzu panelden bagimsizdir (HDMI + 12 V + USB dokunmatik + PWM).", 25.4, 33.02, 1.6)

EK = {"PB10": "PWR_SCL", "PB11": "PWR_SDA",      # I2C2: sarj entegresi, guc anlasmasi entegresi, bataryanin kendi olceri
      "PB3": "I2C_SCL", "PB4": "I2C_SDA",        # I2C3 (kole): giris kartindaki kumanda islemcisiyle dogrudan baglanti
      "PA0": "CHG_INT_N", "PA1": "PD_ALERT_N",   # kesme girisleri
      "PA4": "PWR_BTN_M",                        # guc dugmesi (0 = basili)
      "PA5": "PD_RESET",                         # 1: guc anlasmasi entegresini sifirla
      "PA6": "ALERT_N",                          # acik savak: giris kartina uyari (batarya dusuk, kapanma basliyor)
      "PA2": "JET_IMON",                         # ADC1_IN2: Jetson akimi (4 A -> 3,0 V)
      "PA3": "JET_VIN_EN",                       # 1: Jetson'a besleme ver (sifirlamada kapali)
      "PA7": "JET_POWER_EN",                     # 1: modul acilir
      "PA8": "JET_SHDN_REQ_N",                   # 0: modul kapanmak istiyor -> POWER_EN indirilir
      "PB0": "JET_RESET", "PB1": "JET_RECOVERY", # 1: SYS_RESET* / FORCE_RECOVERY* dusuge cekilir
      "PC7": "JET_MODULE_ID",                    # 1: 5-20 V destekli modul; 0: yalniz 5 V'luk eski modul -> besleme VERILMEZ
      "PD2": "JET_RUN",                          # 1: tasiyici 3,3 V'u acik (modul SYS_RESET*'i birakti)
      "PD3": "PWR_FLT_N",                        # 0: Jetson sigortasi hata verdi
      "PB6": "MCU_TX", "PB7": "MCU_RX",          # USART1: Jetson UART1 (seviye ceviriciden)
      "PC6": "FAN_TACH",                         # TIM3_CH1: fan devir darbesi
      "PA9/PA11": "PWR_USB_DM", "PA10/PA12": "PWR_USB_DP"}   # USB: gobegin 2. portu (PA11 = D-, PA12 = D+)
dg = dugum_sayfasi(k, kok, BURASI, ek=EK, besleme="harici", ethernet=True)
C1210 = "Capacitor_SMD:C_1210_3225Metric"
TANTAL = "Capacitor_Tantalum_SMD:CP_EIA-7343-31_Kemet-D"
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J = {"VDD_IN": "+VJET", "GND": "GND", "POWER_EN": "JET_POWER_EN_R", "SYS_RESET*": "JET_SYS_RESET_N", "SHUTDOWN_REQ*": "JET_SHDN_REQ_HV",
     "FORCE_RECOVERY*": "JET_FRC_N", "MODULE_ID": "JET_MODULE_ID", "MOD_SLEEP*": "JET_MOD_SLEEP_N", "SLEEP/WAKE*": "JET_SLEEP_WAKE_N",
     "PCIE0_CLK_P": "M2_CLK_P", "PCIE0_CLK_N": "M2_CLK_N", "PCIE0_RST*": "M2_RST_N", "PCIE0_CLKREQ*": "M2_CLKREQ_N", "PCIE_WAKE*": "PCIE_WAKE_N",
     "USB0_D_P": "USBC_DP", "USB0_D_N": "USBC_DM", "GPIO00": "USB0_VBUS_DET_N", "USB1_D_P": "HUB_UP_DP", "USB1_D_N": "HUB_UP_DM",
     "UART1_TXD": "JET_UART_TX_1V8", "UART1_RXD": "JET_UART_RX_1V8", "UART2_TXD": "JET_DBG_TX", "UART2_RXD": "JET_DBG_RX", "GPIO14": "JET_FAN_PWM_1V8", "GPIO13": "JET_BL_PWM_1V8",
     "DP1_TXD0_P": "HDMI_D2_J_P", "DP1_TXD0_N": "HDMI_D2_J_N", "DP1_TXD1_P": "HDMI_D1_J_P", "DP1_TXD1_N": "HDMI_D1_J_N",
     "DP1_TXD2_P": "HDMI_D0_J_P", "DP1_TXD2_N": "HDMI_D0_J_N", "DP1_TXD3_P": "HDMI_CK_J_P", "DP1_TXD3_N": "HDMI_CK_J_N",
     "DP1_AUX_P": "HDMI_SCL_3V3", "DP1_AUX_N": "HDMI_SDA_3V3", "DP1_HPD": "HDMI_HPD_N_1V8"}   # HDMI kipi (Ekran sayfasi)
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    "HS_IND/CFG_SEL1": "HUB_CFG1", "SCL/SMBCLK/CFG_SEL0": "HUB_CFG0", "SDA/SMBDATA/NON_REM1": "HUB_NR1", "SUSP_IND/LOCAL_PWR/NON_REM0": "HUB_NR0",
}, "Package_DFN_QFN:QFN-36-1EP_6x6mm_P0.5mm_EP3.7x3.7mm")
g = Izgara(390, 215, sutun=14)
k.koy(cv, "Device:Crystal_GND24", "Y", "24 MHz", *g.yer(), {"1": "HUB_XI", "3": "HUB_XO", "2": "GND", "4": "GND"}, "Crystal:Crystal_SMD_3225-4Pin_3.2x2.5mm")
k.C(cv, g, "18p", "HUB_XI"); k.C(cv, g, "18p", "HUB_XO")
k.R(cv, g, "12k 1%", "HUB_RBIAS", "GND"); k.C(cv, g, "100n", "HUB_CRFILT"); k.C(cv, g, "100n", "HUB_PLLFILT")
k.R(cv, g, "10k", "+3V3_JET", "HUB_RESET_N"); k.R(cv, g, "100k", "HUB_RESET_N", "GND"); k.R(cv, g, "1k", "+3V3_JET", "HUB_VBUS_DET")
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    k.R(cv, g, "75R", "BB_KCT_%s" % c, "BB_BS")
k.C(cv, g, "1n 2kV", "BB_BS", fp=C1206)

cv.metin("SEVIYE CEVIRICI (TXS0104E, 1,8 V <-> 3,3 V): Jetson UART1 <-> guc islemcisi (USART1), fan PWM (GPIO14), ekran parlakligi PWM (GPIO13). Jetson kapaliyken uclarini birakir.", 30, 400)
g = Izgara(50, 445, sutun=10)
k.parca(cv, g, "Logic_LevelTranslator:TXS0104EPW", "U", "TXS0104EPW", {"V_{CCA}": "+1V8_JET", "V_{CCB}": "+3V3", "OE": "+1V8_JET", "GND": "GND",
        "A1": "JET_UART_TX_1V8", "B1": "MCU_RX", "A2": "JET_UART_RX_1V8", "B2": "MCU_TX", "A3": "JET_BL_PWM_1V8", "B3": "BL_PWM_3V3", "A4": "JET_FAN_PWM_1V8", "B4": "FAN_PWM_3V3"},
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k.C(cv, g, "100n", "+1V8_JET"); k.C(cv, g, "100n", "+3V3")
cv.metin("FAN (5 V, 4 uclu: GND, +5V, devir, PWM; Vision ile ayni): PWM Jetson'dan; Jetson kapaliyken 10k asagi cekme fani durdurur.", 30, 490)
g = Izgara(50, 530, sutun=10)
k.parca(cv, g, "Connector_Generic:Conn_01x04", "J", "Fan (PicoBlade)", {"Pin_1": "GND", "Pin_2": "+5V", "Pin_3": "FAN_TACH_K", "Pin_4": "FAN_PWM"},
        "Connector_Molex:Molex_PicoBlade_53047-0410_1x04_P1.25mm_Vertical", dx=8)
k.R(cv, g, "100R", "FAN_PWM_3V3", "FAN_PWM"); k.R(cv, g, "10k", "FAN_PWM", "GND")
k.R(cv, g, "10k", "+3V3", "FAN_TACH"); k.R(cv, g, "10k", "FAN_TACH_K", "FAN_TACH"); k.C(cv, g, "1n", "FAN_TACH")
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
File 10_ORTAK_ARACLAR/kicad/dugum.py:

"""Ortak düğüm devresi: Operfly Bus'a bağlanan her kartta aynı olan kısım.

İçerik: bir Operfly Bus portu, giriş koruması, 5 V ve 3,3 V besleme, düğüm işlemcisi (STM32G0B1CET6),
iki CAN FD alıcı-verici, güvenli eleman (SE050), durum LED'i, hata ayıklama noktaları, isteğe bağlı PPS girişi.

Dışarı verdiği ağlar: +12V (korumalı omurga gerilimi), +5V, +3V3, GND ve kartın `ek` ile istediği işlemci pinleri.
Düğüm işlemcisinin kart işlerine ayrılan boş pinleri: PA0-PA8, PB0, PB1, PB3, PB4, PB6, PB7, PB10, PB11, PC6, PC7, PD2, PD3.
"""
import os

from kart import C0603, C0805, C1206, XAL, Izgara
from sema_uret import Sema

# Düğümün kendi kullandığı pinler (KiCad pin verisindeki alternatif işlevlerle denetlendi).
DUGUM_PINLERI = {
    "PD0": "CAN_A_RX", "PD1": "CAN_A_TX", "PB12": "CAN_B_RX", "PB13": "CAN_B_TX",   # FDCAN1, FDCAN2
    "PB15": "CAN_A_S", "PB2": "CAN_B_S",
    "PB8": "SE_SCL", "PB9": "SE_SDA", "PB5": "SE_ENA",                               # I2C1
    "PA13": "SWDIO", "PA14": "SWCLK", "PF0": "HSE_IN", "PF1": "HSE_OUT", "PF2": "NRST",
    "PB14": "LED_DURUM",
}


def dugum_sayfasi(k, kok, dizin, x=25.4, y=50.8, ek=None, pps=False, ethernet=False, port=True, sonlandirma=False, besleme="omurga", ldo33=True):
    """k: Kart, kok: kök Sema. ek: {işlemci pini: ağ adı} karta özel bağlantılar. Sayfayı yazar ve döndürür.

    port=False: omurga portu bu sayfaya konmaz (Hub gibi portlarını kendi çizen kartlar); kart +12V_BUS ve CAN ağlarını
    kendi sağlar. sonlandirma=True: CAN sonlandırma dirençleri dizilir, toplam 60 ohm (yalnızca Hub);
    sonlandirma=120: 120 ohm dizilir (iki uçlu kısa bağlantının bir ucu olan kartlar, ör. PC adaptörü).
    besleme="kart": port +12V ucu +12V_BUS ağına çıkar ama giriş diyodu bu sayfaya konmaz; kart +12V ağını kendi (daha yüksek
    akımlı) giriş korumasıyla +12V_BUS'tan üretir (ör. Vision).
    besleme="harici": kart omurgadan beslenmez; +5V ve +3V3 ağlarını kart sağlar, port +12V uçları bağlanmaz.
    ethernet=True: omurga fişinin dört Ethernet çifti ETH_A+ ... ETH_D- ağlarına çıkar; ethernet=2: yalnızca A ve B.
    ldo33=False: 3,3 V regülatörü bu sayfaya konmaz; +3V3 ağını kart kendi (daha güçlü) regülatörüyle +5V'tan üretir.
    """
    harici = besleme == "harici"
    kart_korumasi = besleme == "kart"
    s = Sema(k.P, "Dugum devresi (omurga, besleme, islemci, CAN, guvenli eleman)", kagit="A1", tarih=k.T, ust=kok, ad="Dugum", genel_etiket=True)
    kok.alt_sayfa(s, "dugum.kicad_sch", x, y)
    ek = dict(ek or {})
    cakisan = set(ek) & set(DUGUM_PINLERI)
    assert not cakisan, "düğümün kendi pinleri karta verilemez: %s" % cakisan

    s.metin("OMURGA PORTU ve GIRIS KORUMASI: ters baglanti diyotu, 18 V kirpma diyotu. +12V korumali omurga gerilimidir.", 30, 30)
    baglanti = {"+12V": "+12V_BUS", "GND": "GND", "CAN_A_H": "CAN_A_H", "CAN_A_L": "CAN_A_L", "CAN_B_H": "CAN_B_H", "CAN_B_L": "CAN_B_L"}
    if pps:
        baglanti["PPS"] = "PPS_BUS"
    if ethernet:   # True: dort cift (gigabit); 2: yalnizca A ve B ciftleri (100 Mbit), C ve D bos kalir
        baglanti.update({"ETH_%s%s" % (c, i): "ETH_%s%s" % (c, i) for c in ("AB" if ethernet == 2 else "ABCD") for i in "+-"})
    if harici:
        del baglanti["+12V"]
    if port:
        k.koy(s, "operfly:Operfly_Bus_20", "J", "Operfly Bus", 70, 80, baglanti, "Connector_Harwin:Harwin_Gecko_G125-MS12005M2P_2x10_P1.25mm_Vertical")
    if not harici:
        g = Izgara(130, 70, sutun=12)
        if not kart_korumasi:
            k.iki(s, g, "Device:D_Schottky", "D", "B360A (60 V, 3 A)", "+12V", "+12V_BUS", "Diode_SMD:D_SMA")
        k.iki(s, g, "Device:D_TVS", "D", "SMBJ18A", "+12V", "GND", "Diode_SMD:D_SMB")
        k.C(s, g, "10u 50V", "+12V", fp=C1206); k.C(s, g, "100n 50V", "+12V", fp=C0603)
        for ag in ("+12V_BUS", "+12V", "GND"):
            k.bayrak(s, g, ag)

        if ldo33:
            s.metin("BESLEME: 12 V -> 5 V (AP63205, 2 A) -> 3,3 V (LP5907, 250 mA). 3,3 V'ta daha fazla akim isteyen kart kendi regulatorunu ekler.", 30, 125)
        else:
            s.metin("BESLEME: 12 V -> 5 V (AP63205, 2 A). 3,3 V bu kartta kendi sayfasindaki daha guclu regulatorle +5V'tan uretilir.", 30, 125)
        g = Izgara(50, 160, sutun=14)
        k.parca(s, g, "Regulator_Switching:AP63205WU", "U", "AP63205QWU",
                {"IN": "+12V", "EN": "EN_5V", "GND": "GND", "SW": "SW_5V", "BST": "BST_5V", "FB": "+5V"}, "Package_TO_SOT_SMD:TSOT-23-6")
        k.R(s, g, "100k", "+12V", "EN_5V"); k.C(s, g, "10u 50V", "+12V", fp=C1206); k.C(s, g, "100n", "BST_5V", "SW_5V")
        k.iki(s, g, "Device:L", "L", "4u7 XAL4020-472", "SW_5V", "+5V", XAL)
        k.C(s, g, "22u 16V", "+5V", fp=C1206); k.C(s, g, "22u 16V", "+5V", fp=C1206); k.bayrak(s, g, "+5V")
        if ldo33:
            k.parca(s, g, "Regulator_Linear:LP5907MFX-3.3", "U", "LP5907MFX-3.3", {"IN": "+5V", "EN": "+5V", "GND": "GND", "OUT": "+3V3"}, "Package_TO_SOT_SMD:SOT-23-5")
            k.C(s, g, "1u", "+5V"); k.C(s, g, "1u", "+3V3")

    else:
        g = Izgara(130, 70, sutun=12)
        k.bayrak(s, g, "GND")
    s.metin("DUGUM ISLEMCISI (STM32G0B1CET6): omurgaya iki CAN FD hattiyla baglanir, kimligini guvenli elemanla kanitlar.", 30, 215)
    ag = dict(DUGUM_PINLERI)
    if pps:
        ag["PA15"] = "PPS_IN"                                                       # TIM2_CH1
    ag.update(ek)
    ag.update({"VDD": "+3V3", "VBAT": "+3V3", "VREF+": "+3V3", "VSS": "GND"})
    lid = k.lib(s, "MCU_ST_STM32G0:STM32G0B1CETx")
    eksik = set(ag) - {ad for _no, ad, _x, _y, _a in s.pinler[lid]}
    assert not eksik, eksik
    k.koy(s, lid, "U", "STM32G0B1CET6", 110, 300, ag, "Package_QFP:LQFP-48_7x7mm_P0.5mm")
    g = Izgara(200, 250, sutun=12)
    for deger in ("4u7", "100n", "100n", "100n"):
        k.C(s, g, deger, "+3V3", fp=C0603 if deger == "4u7" else "Capacitor_SMD:C_0402_1005Metric")
    k.koy(s, "Device:Crystal_GND24", "Y", "16 MHz", *g.yer(), {"1": "HSE_IN", "3": "HSE_OUT", "2": "GND", "4": "GND"}, "Crystal:Crystal_SMD_3225-4Pin_3.2x2.5mm")
    k.C(s, g, "10p", "HSE_IN"); k.C(s, g, "10p", "HSE_OUT")
    k.R(s, g, "10k", "+3V3", "NRST"); k.C(s, g, "100n", "NRST")
    g.satir()
    k.iki(s, g, "Device:LED", "D", "LED yesil", "LED_DURUM", "LED_DURUM_A", "LED_SMD:LED_0603_1608Metric"); k.R(s, g, "1k", "+3V3", "LED_DURUM_A")
    for a in ("SWDIO", "SWCLK", "NRST"):
        k.olcum_noktasi(s, g, a)
    if pps:
        x0, y0 = g.yer(); g.yer()
        k.koy(s, "74xGxx:74LVC1G17", "U", "74LVC1G17", x0 + 15, y0, {"2": "PPS_BUF_IN", "4": "PPS_IN", "5": "+3V3", "3": "GND"}, "Package_TO_SOT_SMD:SOT-353_SC-70-5")
        k.R(s, g, "100R", "PPS_BUS", "PPS_BUF_IN"); k.R(s, g, "100k", "PPS_BUF_IN", "GND")

    s.metin("CAN FD: iki bagimsiz alici-verici (TJA1051-3). Sessiz mod girisi asagi cekili. Sonlandirma Hub'dadir; yerleri hazir, dizilmez.", 400, 30)
    g = Izgara(420, 70, sutun=12)
    for h in ("A", "B"):
        k.parca(s, g, "Interface_CAN_LIN:TJA1051TK-3", "U", "TJA1051TK/3", {
            "TXD": "CAN_%s_TX" % h, "RXD": "CAN_%s_RX" % h, "S": "CAN_%s_S" % h, "VCC": "+5V", "VIO": "+3V3", "GND": "GND",
            "CANH": "CAN_%s_H" % h, "CANL": "CAN_%s_L" % h}, "Package_SON:HVSON-8-1EP_3x3mm_P0.65mm_EP1.6x2.4mm", dx=15)
        k.C(s, g, "100n", "+5V"); k.C(s, g, "100n", "+3V3"); k.R(s, g, "10k", "CAN_%s_S" % h, "GND")
        k.koy(s, "Power_Protection:NUP2105L", "D", "NUP2105L", *g.yer(), {"1": "CAN_%s_H" % h, "2": "CAN_%s_L" % h, "3": "GND"}, "Package_TO_SOT_SMD:SOT-23")
        # Yıldız omurgada tek sonlandırma Hub'dadır: toplam 60 ohm (iki ucu sonlandırılmış hatla aynı yük).
        rt = "30R1" if sonlandirma is True else "60R4"
        k.R(s, g, rt, "CAN_%s_H" % h, "CAN_%s_TERM" % h, dnp=not sonlandirma); k.R(s, g, rt, "CAN_%s_L" % h, "CAN_%s_TERM" % h, dnp=not sonlandirma)
        k.C(s, g, "4n7", "CAN_%s_TERM" % h, dnp=not sonlandirma)
        g.satir()

    s.metin("GUVENLI ELEMAN (SE050): kart kimligi ve sertifikasi. SE_ENA sifira cekilince eleman kapanir (sifirlama).", 400, 150)
    g = Izgara(420, 195, sutun=12)
    x0, y0 = g.yer(); g.yer(); g.yer()
    k.koy(s, "operfly:SE050", "U", "SE050E2HQ1", x0 + 20, y0, {"I2C_SDA": "SE_SDA", "I2C_SCL": "SE_SCL", "ENA": "SE_ENA",
          "VIN": "+3V3", "VCC": "SE_VCC", "VOUT": "SE_VCC", "VSS": "GND", "EP": "GND"}, "Package_DFN_QFN:QFN-20-1EP_3x3mm_P0.4mm_EP1.65x1.65mm")
    k.R(s, g, "2k2", "+3V3", "SE_SCL"); k.R(s, g, "2k2", "+3V3", "SE_SDA"); k.R(s, g, "10k", "+3V3", "SE_ENA")
    k.C(s, g, "100n", "+3V3"); k.C(s, g, "2u2", "SE_VCC", fp=C0603)
    s.yaz(os.path.join(dizin, "dugum.kicad_sch"))
    return s

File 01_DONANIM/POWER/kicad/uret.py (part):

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kok.metin("Sematik betikle uretilir: 01_DONANIM/POWER/kicad/uret.py.", 25.4, 33.02, 1.6)

# Düğüm devresi ve karta ayrılan işlemci pinleri (KiCad pin verisindeki alternatif işlevlerle denetlendi).
EK = {"PA0": "VBAT_A_SENS", "PA1": "VBAT_B_SENS",          # ADC1_IN0, ADC1_IN1
      "PB10": "PWR_SCL", "PB11": "PWR_SDA",                # I2C2
      "PB3": "PWR_ALERT_N",
      "PA2": "V12_SENS",                                   # ADC1_IN2: cevirici cikis gerilimi
      "PA3": "SERVO_SENS", "PA4": "SRV_A_SENS", "PA5": "SRV_B_SENS",   # ADC1_IN3..5: servo rayi ve iki regulator
      "PA6": "IBAT_SENS",                                  # ADC1_IN6: 400 A algilayici
      "PB6": "SRV_A_OFF", "PB7": "SRV_B_OFF"}              # 1: ilgili servo regulatorunu kapatir
dg = dugum_sayfasi(k, kok, BURASI, ek=EK)

# --- Giris: iki batarya girisi, ideal diyotlar, giris olcumu -------------------
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cv.metin("202 kHz, bobin 10 uH, akim direnci 4 mR, giris akim siniri 18 A (10 V altinda guc kendiliginden azalir).", 30, 34)
cv.metin("ILK TASLAK: kompanzasyon ve isil hesap benzetimle (LTspice) dogrulanmadan uretime gonderilmez.", 30, 40)
cv.koy(k.lib(cv, "Regulator_Switching:LT8705AxFE"), k.ref("U"), "LT8705AIFE", 130, 130, {
    "VIN": "VIN_SW", "CSPIN": "VIN", "CSNIN": "VIN_SW", "~{SHDN}": "CV_SHDN", "FBIN": "CV_FBIN", "MODE": "CV_LDO33", "SYNC": "GND",
    "RT": "CV_RT", "SS": "CV_SS", "INTVCC": "CV_INTVCC", "GATEVCC": "CV_INTVCC", "EXTVCC": "12V_OUT", "LDO33": "CV_LDO33",
    "TG1": "CV_TG1", "BOOST1": "CV_BOOST1", "SW1": "CV_SW1", "BG1": "CV_BG1", "CSP": "CV_CSP", "CSN": "CV_CSN",
    "BG2": "CV_BG2", "SW2": "CV_SW2", "BOOST2": "CV_BOOST2", "TG2": "CV_TG2",
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sv.metin("SERVO CIKISI (XT30) ve olcum; 400 A TEMASSIZ AKIM ALGILAYICI girisi (5 V beslemeli, analog cikisli harici algilayici; parca secilecek).", 30, 335)
g = Izgara(50, 370, sutun=16, dx=24)
x, y = g.yer()
k.koy(sv, "Connector_Generic:Conn_01x02", "J", "Servo rayi (XT30)", x + 5, y, {"Pin_1": "SERVO_V", "Pin_2": "GND"}, "Connector_AMASS:AMASS_XT30U-M_1x02_P5.0mm_Vertical")
k.C(sv, g, "47u 16V", "SERVO_V", fp=C1210); k.C(sv, g, "47u 16V", "SERVO_V", fp=C1210)
k.R(sv, g, "30k 1%", "SERVO_V", "SERVO_SENS"); k.R(sv, g, "10k 1%", "SERVO_SENS", "GND"); k.C(sv, g, "100n", "SERVO_SENS")
k.olcum_noktasi(sv, g, "SERVO_V"); k.bayrak(sv, g, "VIN")
x, y = g.yer(); g.yer()
k.koy(sv, "Connector_Generic:Conn_01x03", "J", "Akim algilayici", x + 10, y, {"Pin_1": "+5V", "Pin_2": "IBAT_RAW", "Pin_3": "GND"},
      "Connector_JST:JST_GH_SM03B-GHS-TB_1x03-1MP_P1.25mm_Horizontal")
k.R(sv, g, "10k 1%", "IBAT_RAW", "IBAT_SENS"); k.R(sv, g, "20k 1%", "IBAT_SENS", "GND"); k.C(sv, g, "100n", "IBAT_SENS")
sv.yaz(os.path.join(BURASI, "servo.kicad_sch"))
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
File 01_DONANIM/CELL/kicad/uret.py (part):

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kok.metin("Operfly Cell - 5G hucresel baglanti karti (OPFCEL)", 25.4, 25.4, 3.0)
kok.metin("Sematik betikle uretilir: 01_DONANIM/CELL/kicad/uret.py. Modem M.2 yuvasina takilir; anten kablolari modulun kendi konnektorlerinden cikar.", 25.4, 33.02, 1.6)

EK = {"PA9/PA11": "MCU_USB_DM", "PA10/PA12": "MCU_USB_DP",   # USB FS ana bilgisayar (PA11 = D-, PA12 = D+): modemin AT kanali
      "PA4": "MODEM_PWR_OFF",                                # 1: modem regulatorunu kapat (sifirlamada acik)
      "PA5": "MODEM_ON",                                     # FULL_CARD_POWER_OFF#: 1 = modem calisir, 0 = kapanir (sifirlamada 0)
      "PA6": "MODEM_RST",                                    # 1: RESET# dusuge cekilir
      "PA7": "MODEM_RF_EN",                                  # W_DISABLE1#: 0 = radyo kapali (ucak kipi); acik savak sur
      "PB0": "MODEM_WAKE_N",                                 # WAKE_ON_WAN#: modem bildirimi (1 s dusuk darbe)
      "PA0": "MODEM_VSENS",                                  # ADC1_IN0: modem beslemesi / 2
      "PA1": "USB_SEL",                                      # 1: servis USB'sine kablo takili (modemin USB'si oraya bagli)
      "PB3": "ETH_PG"}                                       # 1: Ethernet denetleyicinin 3,3 V'u hazir
dg = dugum_sayfasi(k, kok, BURASI, ek=EK, ethernet=True)

# --- Modem: besleme, M.2 yuvası, denetim, SIM, USB ----------------------------------
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k.bayrak(md, g, V38); k.olcum_noktasi(md, g, V38)

md.metin("MODEM YUVASI (M.2 Key B, 3052): uc numaralari modem kilavuzundaki gibidir. Yuva sembolundeki adlar bilgisayar tarafina goredir:", 30, 150)
md.metin("41/43 modemin PCIe VERICISI, 47/49 modemin PCIe ALICISI. Modem kok (RC) kipinde: PCIE_RST_N ve saat modemden cikar.", 30, 156)
md.metin("VCC yaninda: 2 x 220 uF dusuk ESR + seramik dizi + 5 V kirpma diyodu (uretici onerisi). Bos birakilan uclar kilavuza gore bos kalir.", 30, 162)
S = {"3.3V": V38, "GND": "GND", "~{FULL_CARD_POWER_OFF}": "MODEM_ON", "~{RESET}": "MODEM_RESET_N", "~{W_DISABLE1}": "MODEM_RF_EN",
     "USB_D+": "MODEM_USB_DP_M", "USB_D-": "MODEM_USB_DM_M", "10": "MODEM_LED_N", "23": "MODEM_WAKE_N",
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
et.metin("PCIe ETHERNET DENETLEYICI (RTL8111H-CG, 1 Gbit): modem PCIe kok aygitidir, bu entegreyi kendisi surer (modemde AT komutuyla acilir).", 30, 130)
et.metin("Modemin vericisi (41/43) dogrudan HSIP/HSIN'e gelir (kondansator modemin icinde); denetleyicinin vericisi 220 nF ile modemin alicisina gider.", 30, 136)
et.metin("PCIE_RST_N kok kipinde modemin acik savak cikisidir: 4k7 yukari cekme. Cevre degerleri (RSET, 1,0 V kondansatorleri, ISOLATEB) README'de 'dogrulanacak'.", 30, 142)
E = {"HSIP": "PCIE_MTX_P", "HSIN": "PCIE_MTX_N", "HSOP": "ETH_TX_P", "HSON": "ETH_TX_N", "REFCLK_P": "PCIE_CLK_P", "REFCLK_N": "PCIE_CLK_N",
     "PERSTB": "PCIE_RST_N", "CLKREQB": "PCIE_CLKREQ_N", "LANWAKEB": "PCIE_WAKE_N", "ISOLATEB": "ETH_ISOLATE_N",
     "CKXTAL1": "ETH_XI", "CKXTAL2": "ETH_XO", "RSET": "ETH_RSET", "LED0": "ETH_LED0", "LED2": "ETH_LED2", "REGOUT": "ETH_1V0",
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k.R(et, g, "4k7", V33E, "PCIE_RST_N"); k.R(et, g, "10k", V33E, "PCIE_CLKREQ_N"); k.R(et, g, "10k", V33E, "PCIE_WAKE_N")
k.R(et, g, "1k", V33E, "ETH_ISOLATE_N"); k.R(et, g, "15k", "ETH_ISOLATE_N", "GND")
k.R(et, g, "2k49 1%", "ETH_RSET", "GND")
k.koy(et, "Device:Crystal_GND24", "Y", "25 MHz 30 ppm", *g.yer(), {"1": "ETH_XI", "3": "ETH_XO", "2": "GND", "4": "GND"}, "Crystal:Crystal_SMD_3225-4Pin_3.2x2.5mm")
k.C(et, g, "27p", "ETH_XI"); k.C(et, g, "27p", "ETH_XO")
g.satir()
for _ in range(3):
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
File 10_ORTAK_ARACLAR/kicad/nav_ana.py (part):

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    kok.metin("Sematik betikle uretilir: 01_DONANIM/%s/kicad/uret.py." % klasor, 25.4, 33.02, 1.6)

    # Düğüm devresi ve karta ayrılan işlemci pinleri (KiCad pin verisindeki alternatif işlevlerle denetlendi).
    EK = {"PA2": "GNSS_RXD1", "PA3": "GNSS_TXD1",              # USART2_TX -> modul RXD1, USART2_RX <- modul TXD1 (COM1: olcum ve komut)
          "PA1": "GNSS_CTS1", "PA0": "GNSS_RTS1",              # USART2_RTS -> modul CTS1, USART2_CTS <- modul RTS1
          "PB6": "GNSS_RXD2", "PB7": "GNSS_TXD2",              # USART1_TX -> modul RXD2, USART1_RX <- modul TXD2 (COM2: RTK duzeltmeleri)
          "PB3": "GNSS_PPS",                                   # TIM2_CH2: alicinin kendi saniye darbesi (omurga darbesi PA15, TIM2_CH1)
          "PB4": "PPS_OE_N",                                   # 0: saniye darbesi omurgaya surulur
          "PB0": "GNSS_NRST", "PB1": "GNSS_RDY",
          "PA4": "ANT_BIAS_EN",                                # 1: antene 3,3 V besleme verilir
          "PA8": "GNSS_EVENT",                                 # TIM1_CH1: aliciya olay isareti (ornegin kamera tetigi)
          "PC6": "GNSS_LOGBTN", "PC7": "GNSS_LOGLED",
          "PB10": "MAG_SCL", "PB11": "MAG_SDA", "PA6": "MAG_DRDY", "PA7": "MAG_RST_N"}   # I2C2
    if baz:   # Base: pusula yok; dis besleme gerilimi olculur
        for p in ("PB10", "PB11", "PA6", "PA7"):
            del EK[p]
        EK["PA6"] = "VEXT_SENS"                              # ADC1_IN6: dis besleme girisi / 11
    dg = dugum_sayfasi(k, kok, burasi, ek=EK, pps=True, ldo33=False)

    # --- GNSS: alıcı modülü, besleme, antenler, saniye darbesi -------------------
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        cv.metin("Ters baglantida diyot karti korur, kirpma diyodu sigortayi attirir. VEXT_SENS = giris gerilimi / 11 (islemci olcer).", 300, 40)
        g = Izgara(320, 80, sutun=10)
        x, y = g.yer(); g.yer()
        k.koy(cv, "Connector_Generic:Conn_01x02", "J", "Dis besleme (XT30)", x + 5, y, {"Pin_1": "VEXT_IN", "Pin_2": "GND"}, "Connector_AMASS:AMASS_XT30U-M_1x02_P5.0mm_Vertical")
        k.iki(cv, g, "Device:Polyfuse", "F", "2 A tutma (1812)", "VEXT_IN", "VEXT_F", "Fuse:Fuse_1812_4532Metric")
        k.iki(cv, g, "Device:D_TVS", "D", "SMBJ18A", "VEXT_F", "GND", "Diode_SMD:D_SMB")
        k.iki(cv, g, "Device:D_Schottky", "D", "B360A (60 V, 3 A)", "+12V", "VEXT_F", "Diode_SMD:D_SMA")
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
